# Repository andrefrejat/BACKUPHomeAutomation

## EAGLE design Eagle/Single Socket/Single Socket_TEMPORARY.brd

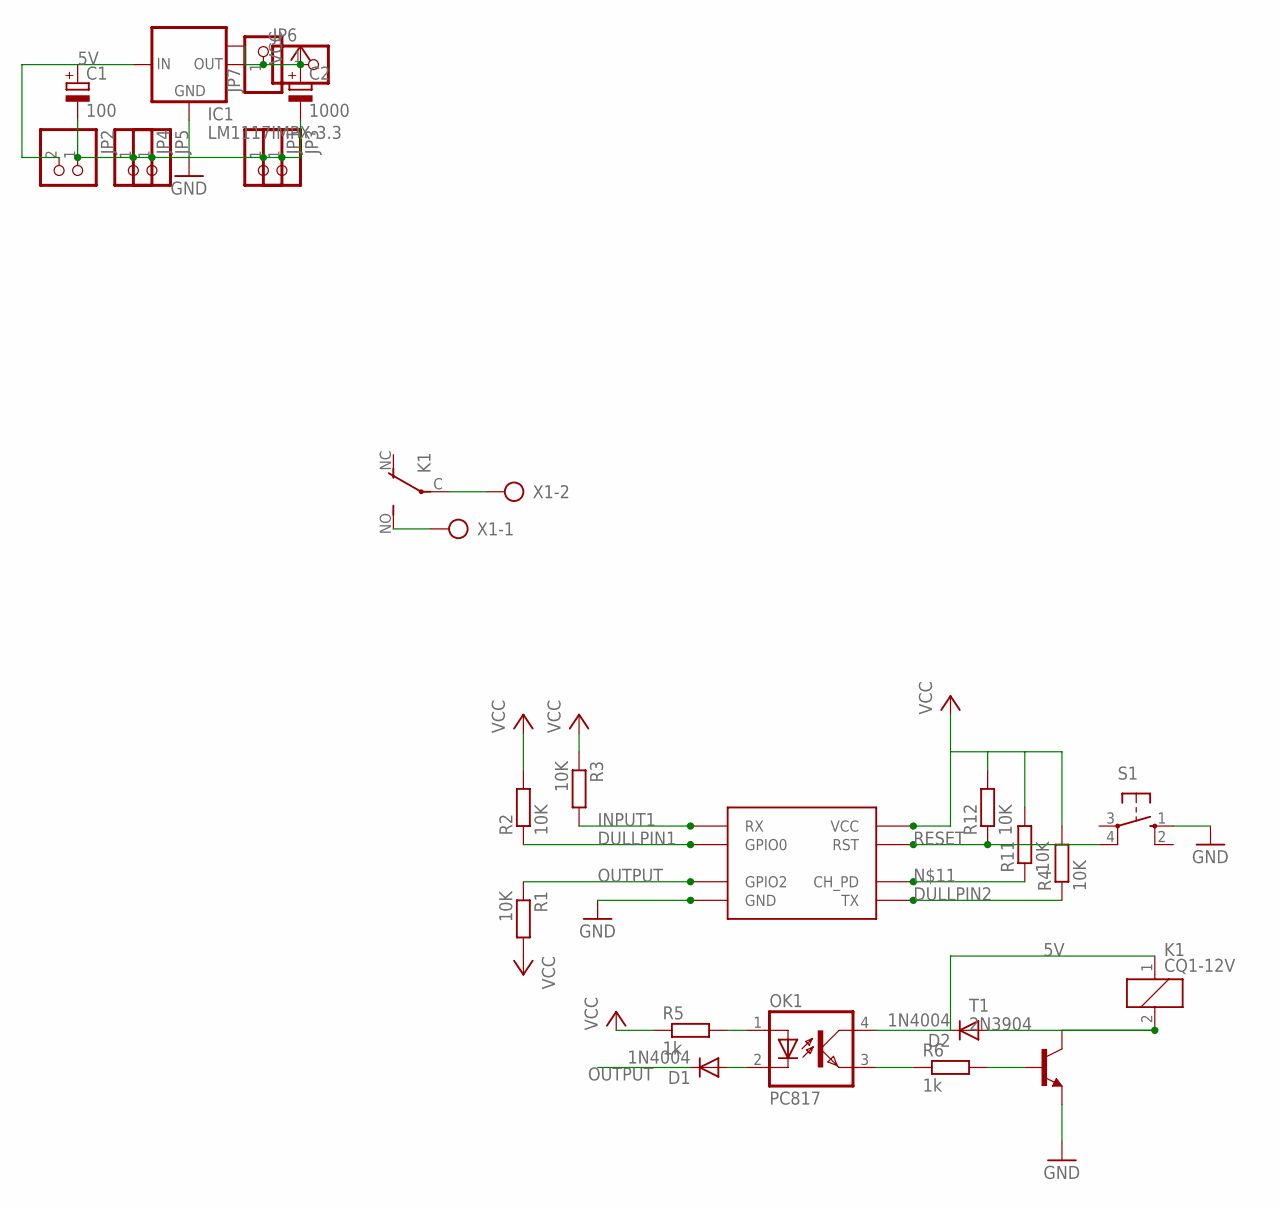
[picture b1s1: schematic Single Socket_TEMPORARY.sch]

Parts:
C1: 100; E5-10,5
C2: 1000; E5-10,5
D1, D2: 1N4004; DO41-10
IC1: LM1117IMPX-3.3; SOT223
JP1, JP3, JP4, JP5, JP6, JP7: PINHD-1X1; 1X01
JP2: PINHD-1X2; 1X02
K1: CQ1-12V; CQ1
OK1: PC817; DIL04
R1, R2, R3, R4, R11, R12: 10K; 0207/10
R5, R6: 1k; 0207/10
S1: 10-XX; B3F-10XX; MPN B3F-1000
T1: 2N3904; TO92
U$2: ESP8266
X1: AK500/2-H

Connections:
5V: C1.+, D2.C, IC1.3 (IN), JP2.2, K1.1, OK1.4 (COL)
DULLPIN1: R2.1, U$2.GPIO0
DULLPIN2: R4.1, U$2.TX
GND: C1.-, C2.-, IC1.1 (GND), JP1.1, JP2.1, JP3.1, JP4.1, JP5.1, S1.1 (S), T1.3 (E), U$2.GND
INPUT1: R3.2, U$2.RX
unnamed: K1.C, X1.2
unnamed: K1.NO (S), X1.1
unnamed: OK1.1 (A), R5.2
unnamed: OK1.3 (EMIT), R6.1
unnamed: D1.A, OK1.2 (C)
unnamed: R6.2, T1.2 (B)
unnamed: D2.A, K1.2, T1.1 (C)
unnamed: R11.1, U$2.CH_PD
OUTPUT: D1.C, R1.1, U$2.GPIO2
RESET: R12.1, S1.4 (P1), U$2.RST
VCC: C2.+, IC1.2 (OUT), IC1.TAB (OUT1), JP6.1, JP7.1, R1.2, R2.2, R3.1, R4.2, R5.1, R11.2, R12.2, U$2.VCC

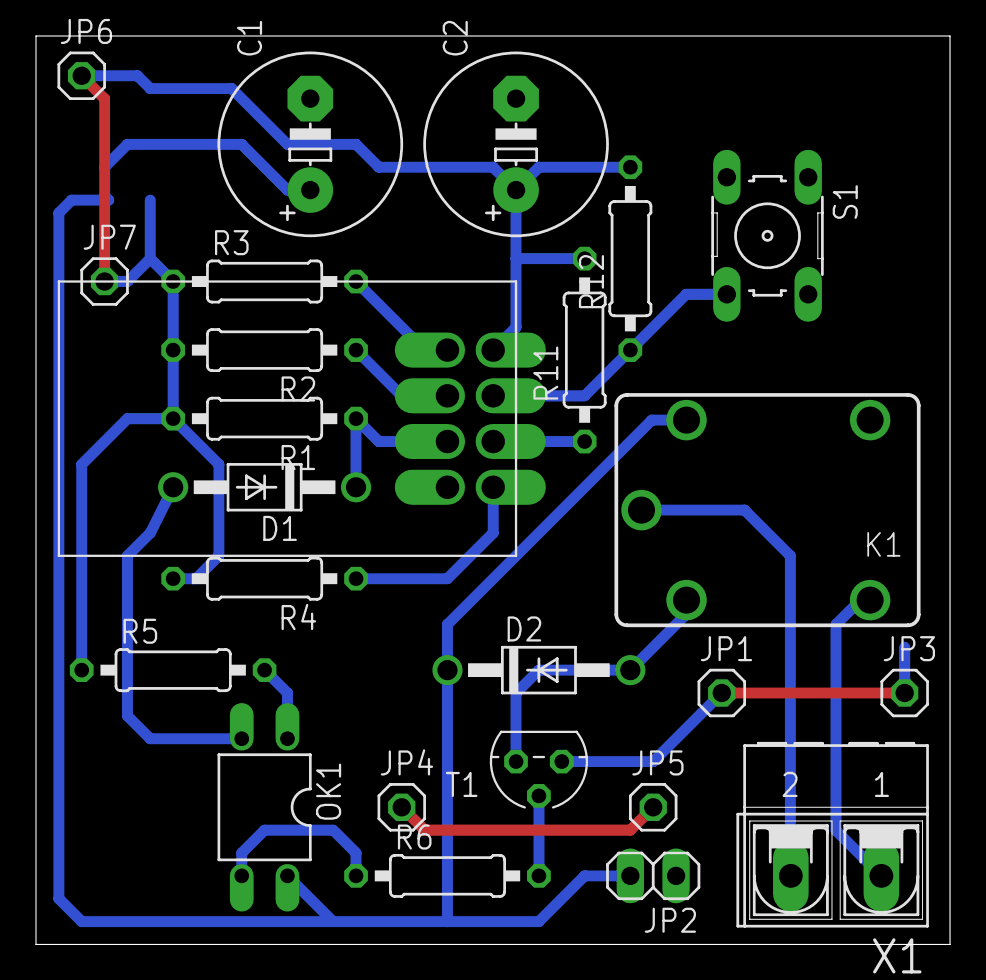
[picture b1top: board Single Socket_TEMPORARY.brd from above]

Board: 2 copper layers, 50.8 x 50.5 mm, 26 parts (1 on the bottom side), 16 nets.

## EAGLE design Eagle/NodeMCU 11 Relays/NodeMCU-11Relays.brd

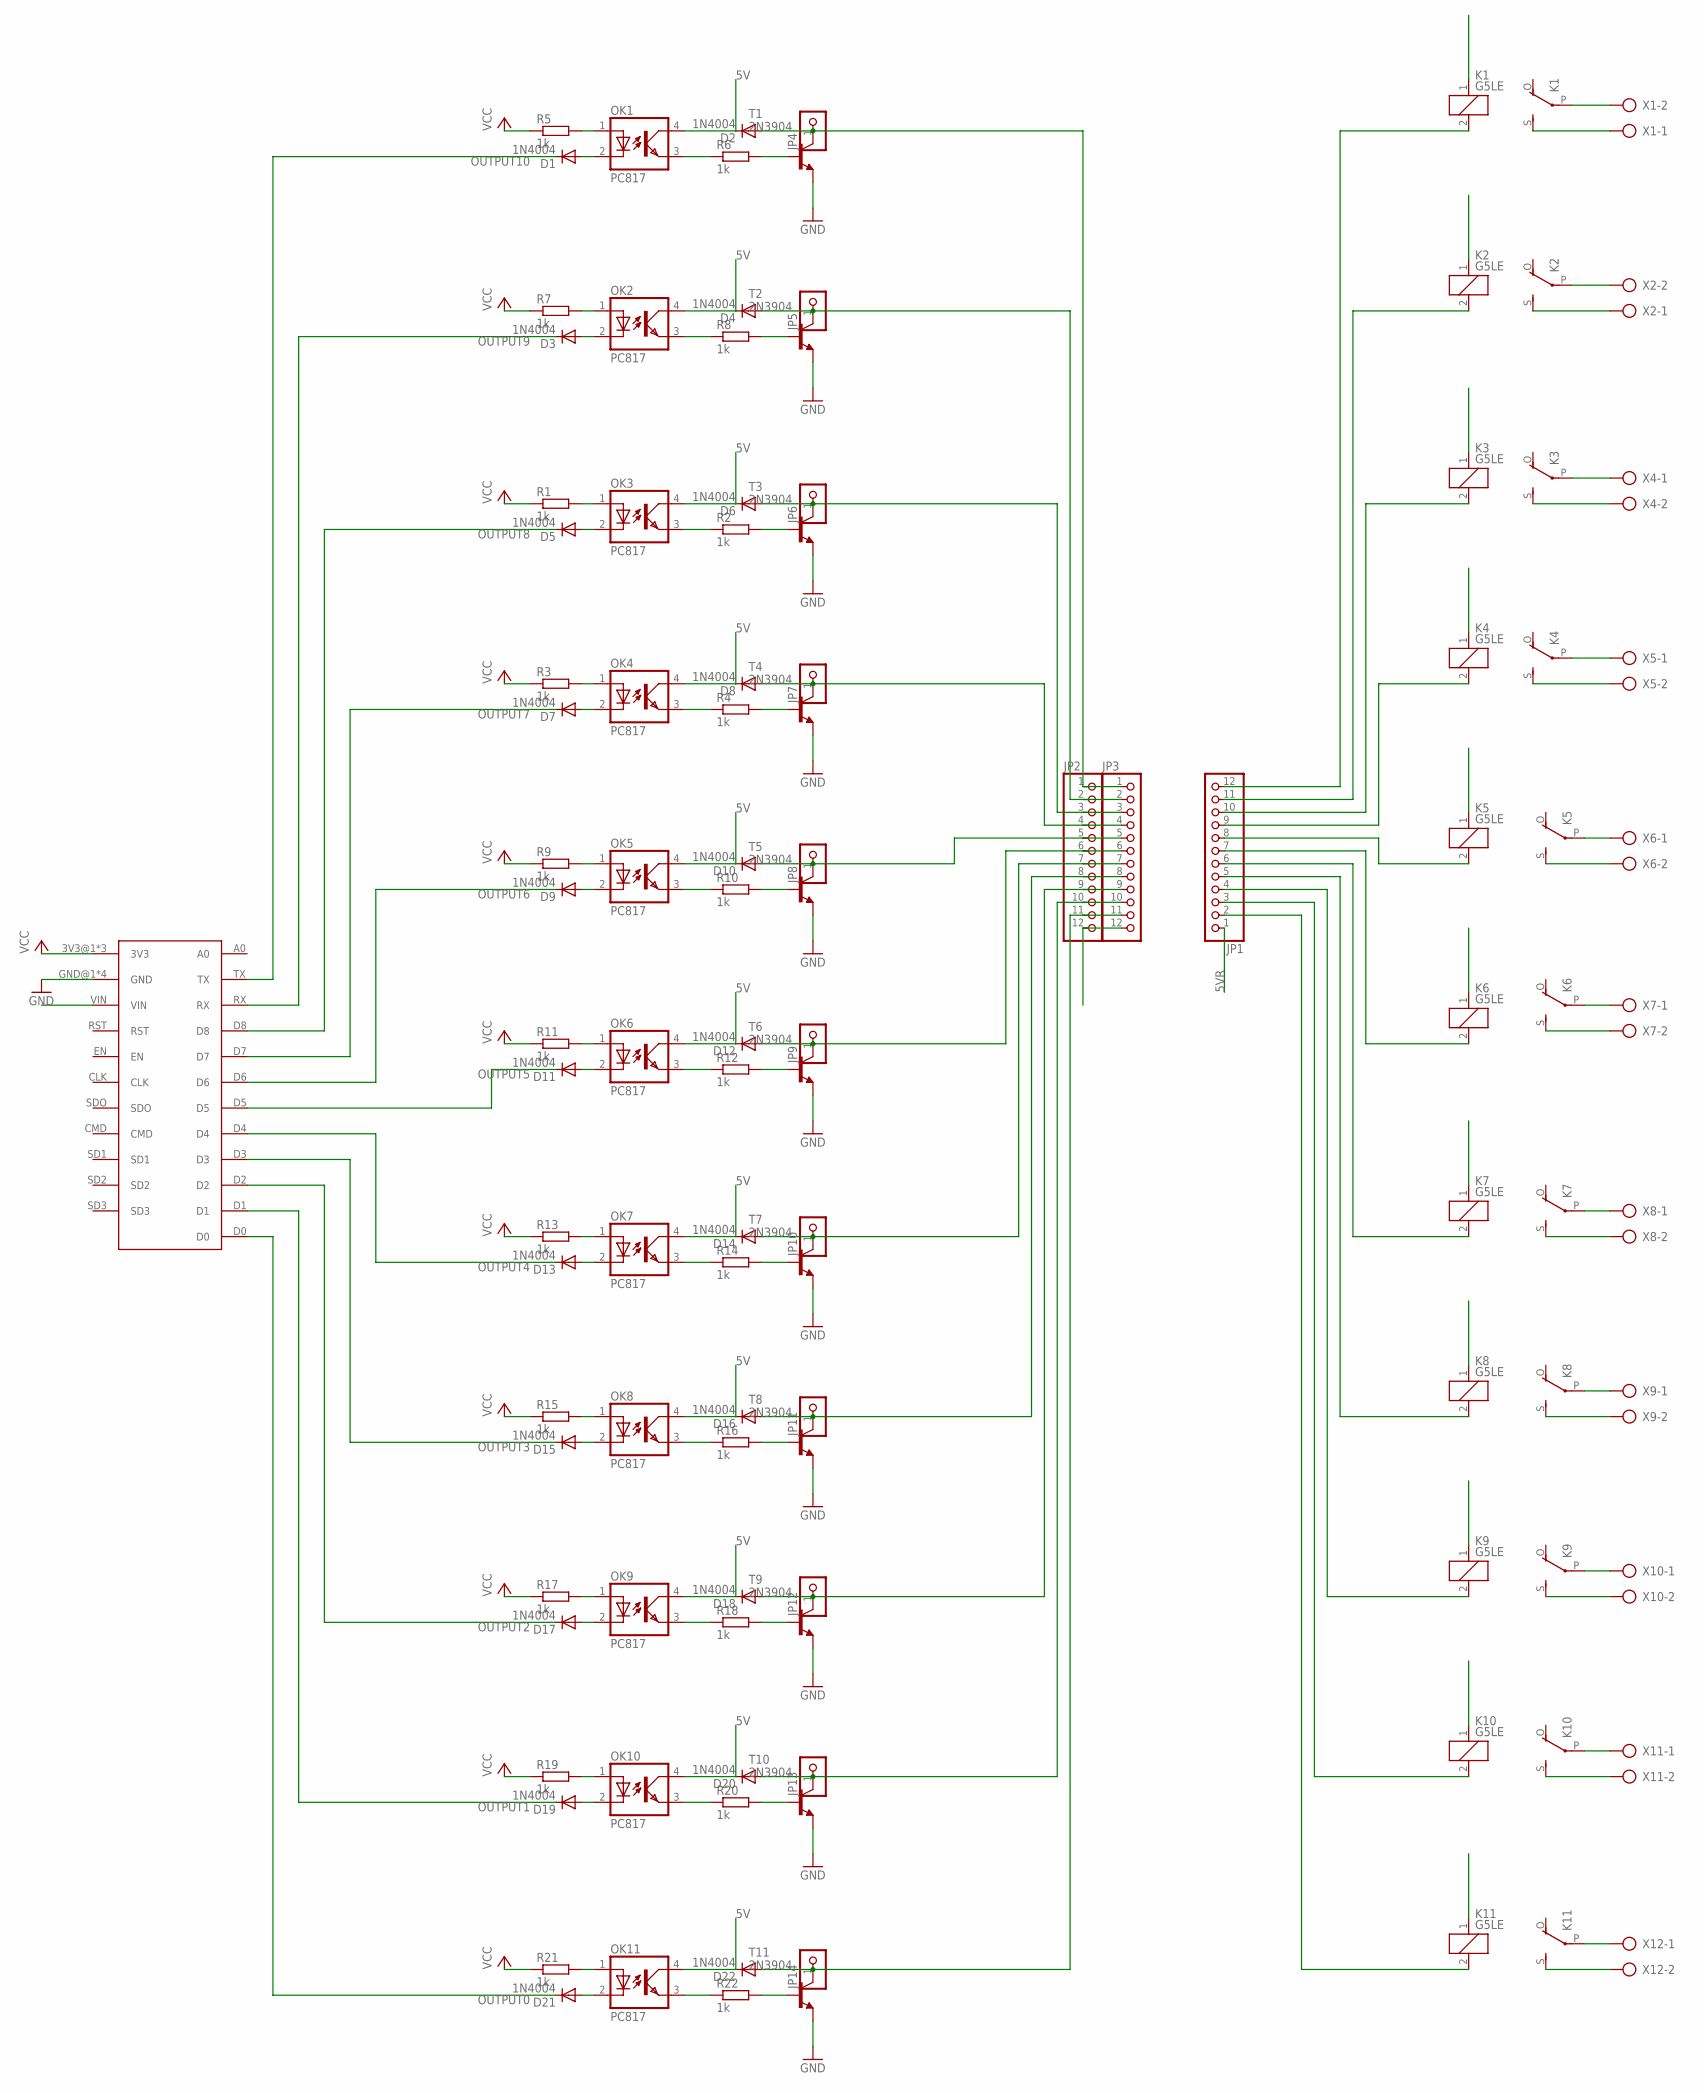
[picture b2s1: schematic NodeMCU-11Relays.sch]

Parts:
D1, D2, D3, D4, D5, D6, D7, D8, D9, D10, D11, D12, D13, D14, D15, D16, D17, D18, D19, D20, D21, D22: 1N4004; DO41-10
JP1, JP2, JP3: PINHD-1X12; 1X12
JP4, JP5, JP6, JP7, JP8, JP9, JP10, JP11, JP12, JP13, JP14: PINHD-1X1; 1X01
K1, K2, K3, K4, K5, K6, K7, K8, K9, K10, K11: G5LE
OK1, OK2, OK3, OK4, OK5, OK6, OK7, OK8, OK9, OK10, OK11: PC817; DIL04
R1, R2, R3, R4, R5, R6, R7, R8, R9, R10, R11, R12, R13, R14, R15, R16, R17, R18, R19, R20, R21, R22: 1k; 0207/10
T1, T2, T3, T4, T5, T6, T7, T8, T9, T10, T11: 2N3904; TO92
U$1: NODEMCU-1.0
X1, X2, X4, X5, X6, X7, X8, X9, X10, X11, X12: AK500/2-H

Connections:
5V: D2.C, D4.C, D6.C, D8.C, D10.C, D12.C, D14.C, D16.C, D18.C, D20.C, D22.C, JP2.12, JP3.12, OK1.4 (COL), OK2.4 (COL), OK3.4 (COL), OK4.4 (COL), OK5.4 (COL), OK6.4 (COL), OK7.4 (COL), OK8.4 (COL), OK9.4 (COL), OK10.4 (COL), OK11.4 (COL), U$1.VIN
5VR: JP1.1, K1.1, K2.1, K3.1, K4.1, K5.1, K6.1, K7.1, K8.1, K9.1, K11.1
GND: T1.3 (E), T2.3 (E), T3.3 (E), T4.3 (E), T5.3 (E), T6.3 (E), T7.3 (E), T8.3 (E), T9.3 (E), T10.3 (E), T11.3 (E), U$1.GND@1 (GND), U$1.GND@2 (GND), U$1.GND@3 (GND), U$1.GND@4 (GND)
unnamed: K1.P, X1.2
unnamed: K1.S, X1.1
unnamed: OK1.1 (A), R5.2
unnamed: OK1.3 (EMIT), R6.1
unnamed: D1.A, OK1.2 (C)
unnamed: OK2.1 (A), R7.2
unnamed: R6.2, T1.2 (B)
unnamed: D2.A, JP2.1, JP3.1, JP4.1, T1.1 (C)
unnamed: OK2.3 (EMIT), R8.1
unnamed: D3.A, OK2.2 (C)
unnamed: OK3.1 (A), R1.2
unnamed: R8.2, T2.2 (B)
unnamed: D4.A, JP2.2, JP3.2, JP5.1, T2.1 (C)
unnamed: K2.S, X2.1
unnamed: K2.P, X2.2
unnamed: OK3.3 (EMIT), R2.1
unnamed: D5.A, OK3.2 (C)
unnamed: R2.2, T3.2 (B)
unnamed: D6.A, JP2.3, JP3.3, JP6.1, T3.1 (C)
unnamed: OK4.1 (A), R3.2
unnamed: OK4.3 (EMIT), R4.1
unnamed: D7.A, OK4.2 (C)
unnamed: R4.2, T4.2 (B)
unnamed: D8.A, JP2.4, JP3.4, JP7.1, T4.1 (C)
unnamed: OK5.1 (A), R9.2
unnamed: OK5.3 (EMIT), R10.1
unnamed: D9.A, OK5.2 (C)
unnamed: R10.2, T5.2 (B)
unnamed: D10.A, JP2.5, JP3.5, JP8.1, T5.1 (C)
unnamed: OK6.1 (A), R11.2
unnamed: OK6.3 (EMIT), R12.1
unnamed: D11.A, OK6.2 (C)
unnamed: R12.2, T6.2 (B)
unnamed: D12.A, JP2.6, JP3.6, JP9.1, T6.1 (C)
unnamed: OK7.1 (A), R13.2
unnamed: OK7.3 (EMIT), R14.1
unnamed: D13.A, OK7.2 (C)
unnamed: R14.2, T7.2 (B)
unnamed: D14.A, JP2.7, JP3.7, JP10.1, T7.1 (C)
unnamed: OK8.1 (A), R15.2
unnamed: OK8.3 (EMIT), R16.1
unnamed: D15.A, OK8.2 (C)
unnamed: R16.2, T8.2 (B)
unnamed: D16.A, JP2.8, JP3.8, JP11.1, T8.1 (C)
unnamed: OK9.1 (A), R17.2
unnamed: OK9.3 (EMIT), R18.1
unnamed: D17.A, OK9.2 (C)
unnamed: R18.2, T9.2 (B)
unnamed: D18.A, JP2.9, JP3.9, JP12.1, T9.1 (C)
unnamed: OK10.1 (A), R19.2
unnamed: OK10.3 (EMIT), R20.1
unnamed: D19.A, OK10.2 (C)
unnamed: R20.2, T10.2 (B)
unnamed: D20.A, JP2.10, JP3.10, JP13.1, T10.1 (C)
unnamed: OK11.1 (A), R21.2
unnamed: OK11.3 (EMIT), R22.1
unnamed: D21.A, OK11.2 (C)
unnamed: R22.2, T11.2 (B)
unnamed: D22.A, JP2.11, JP3.11, JP14.1, T11.1 (C)
unnamed: K3.P, X4.1
unnamed: K4.P, X5.1
unnamed: K5.P, X6.1
unnamed: K6.P, X7.1
unnamed: K7.P, X8.1
unnamed: K8.P, X9.1
unnamed: K9.P, X10.1
unnamed: K10.P, X11.1
unnamed: K11.P, X12.1
unnamed: K3.S, X4.2
unnamed: K4.S, X5.2
unnamed: K5.S, X6.2
unnamed: K6.S, X7.2
unnamed: K7.S, X8.2
unnamed: K8.S, X9.2
unnamed: K9.S, X10.2
unnamed: K10.S, X11.2
unnamed: K11.S, X12.2
unnamed: JP1.2, K11.2
unnamed: JP1.3, K10.2
unnamed: JP1.4, K9.2
unnamed: JP1.5, K8.2
unnamed: JP1.6, K7.2
unnamed: JP1.7, K6.2
unnamed: JP1.8, K5.2
unnamed: JP1.9, K4.2
unnamed: JP1.10, K3.2
unnamed: JP1.11, K2.2
unnamed: JP1.12, K1.2
OUTPUT0: D21.C, U$1.D0
OUTPUT1: D19.C, U$1.D1
OUTPUT2: D17.C, U$1.D2
OUTPUT3: D15.C, U$1.D3
OUTPUT4: D13.C, U$1.D4
OUTPUT5: D11.C, U$1.D5
OUTPUT6: D9.C, U$1.D6
OUTPUT7: D7.C, U$1.D7
OUTPUT8: D5.C, U$1.D8
OUTPUT9: D3.C, U$1.RX
OUTPUT10: D1.C, U$1.TX
VCC: R1.1, R3.1, R5.1, R7.1, R9.1, R11.1, R13.1, R15.1, R17.1, R19.1, R21.1, U$1.3V3@1 (3V3), U$1.3V3@2 (3V3), U$1.3V3@3 (3V3)

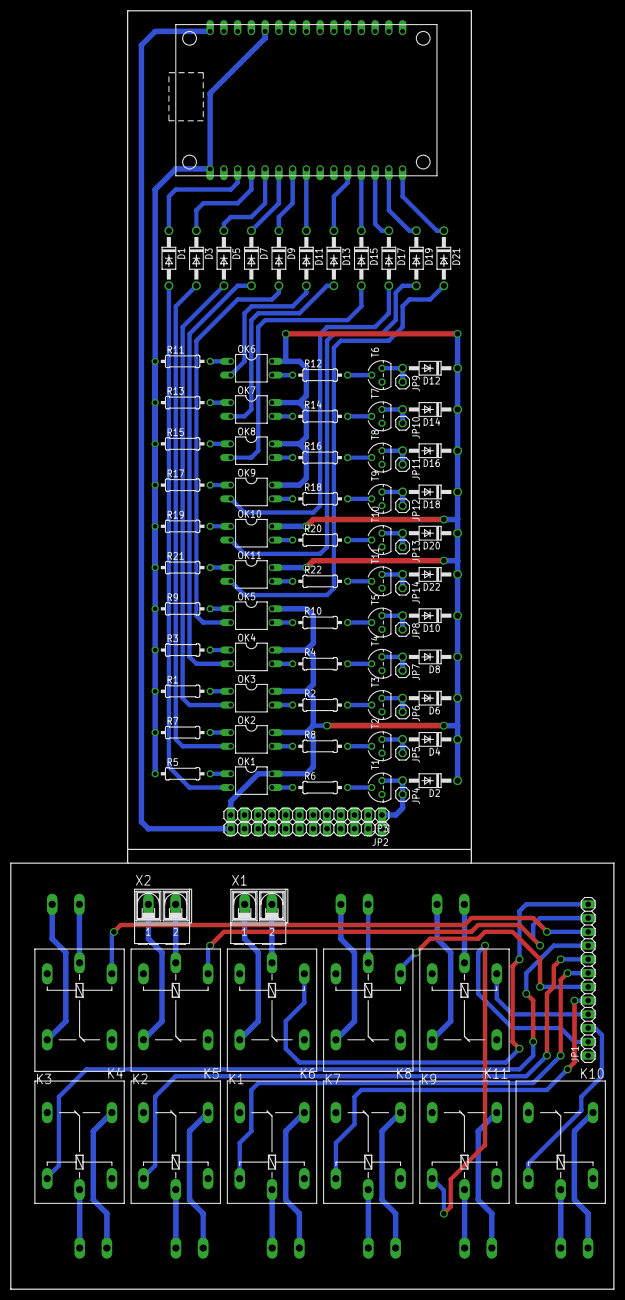
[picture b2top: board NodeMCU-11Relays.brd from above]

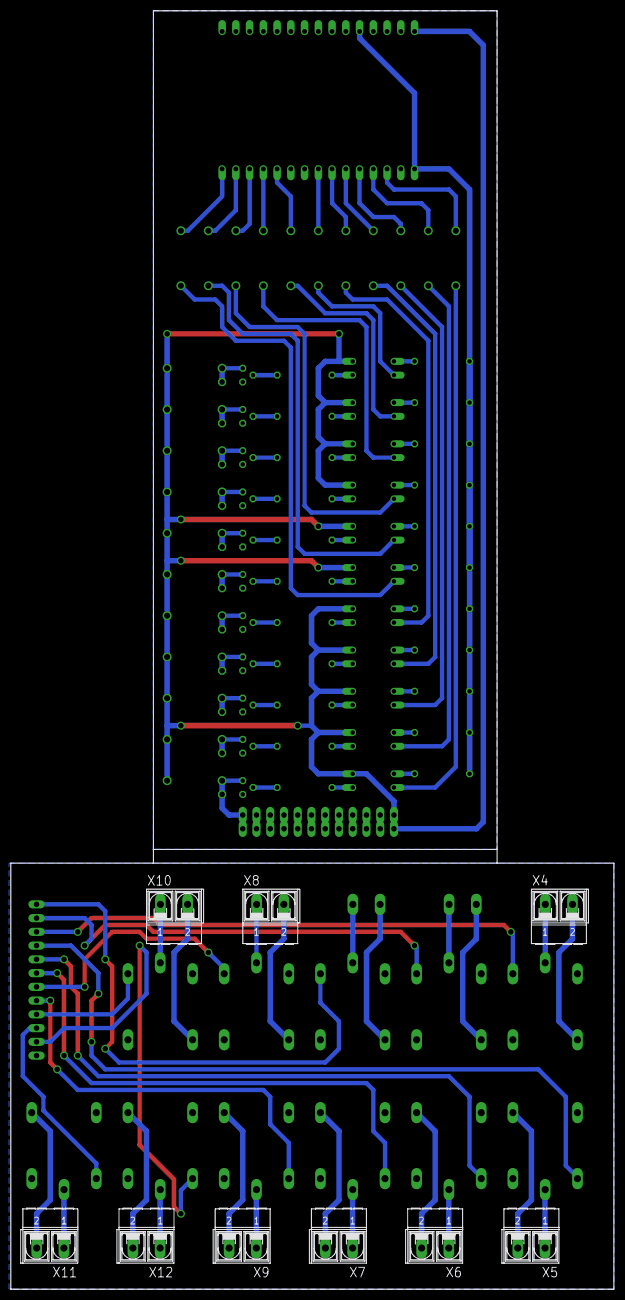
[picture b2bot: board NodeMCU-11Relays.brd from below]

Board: 2 copper layers, 111.4 x 236.2 mm, 103 parts (9 on the bottom side), 103 nets.

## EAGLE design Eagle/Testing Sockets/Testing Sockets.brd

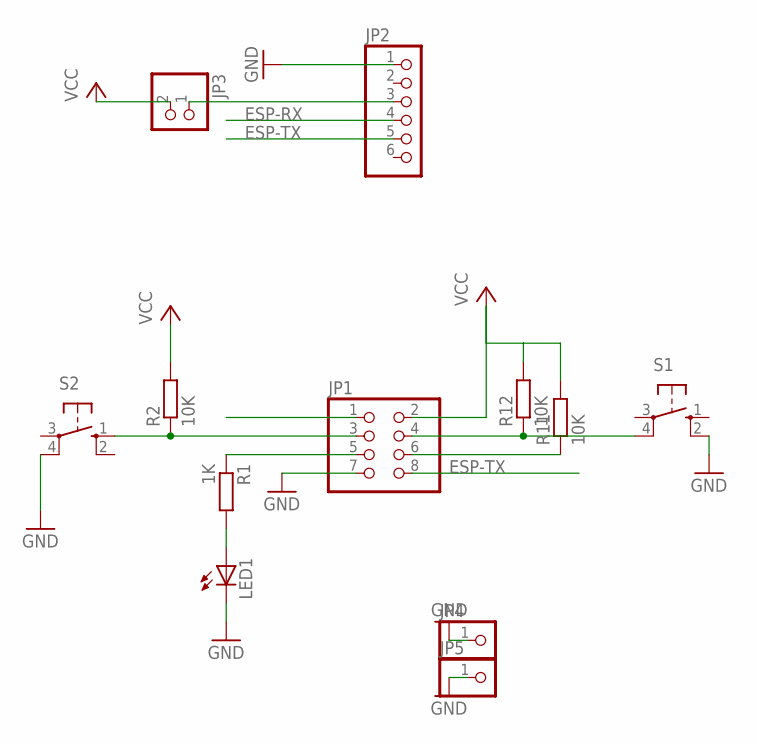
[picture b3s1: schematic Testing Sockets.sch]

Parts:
JP1: PINHD-2X4; 2X04
JP2: PINHD-1X6; 1X06
JP3: PINHD-1X2; 1X02
JP4, JP5: PINHD-1X1; 1X01
LED1: LED5MM
R1: 1K; 0207/10
R2, R11, R12: 10K; 0207/10
S1: 10-XX; B3F-10XX
S2: 10-XX; B3F-10XX; MPN B3F-1000

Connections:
ESP-RX: JP1.1, JP2.4
ESP-TX: JP1.8, JP2.5
GND: JP1.7, JP2.1, JP4.1, JP5.1, LED1.K (C), S1.2 (S1), S2.4 (P1)
unnamed: JP1.5, R1.1
unnamed: LED1.A, R1.2
unnamed: JP2.3, JP3.1
unnamed: JP1.6, R11.1
unnamed: JP1.4, R12.1, S1.4 (P1)
SOCKET1: JP1.3, R2.1, S2.1 (S)
VCC: JP1.2, JP3.2, R2.2, R11.2, R12.2

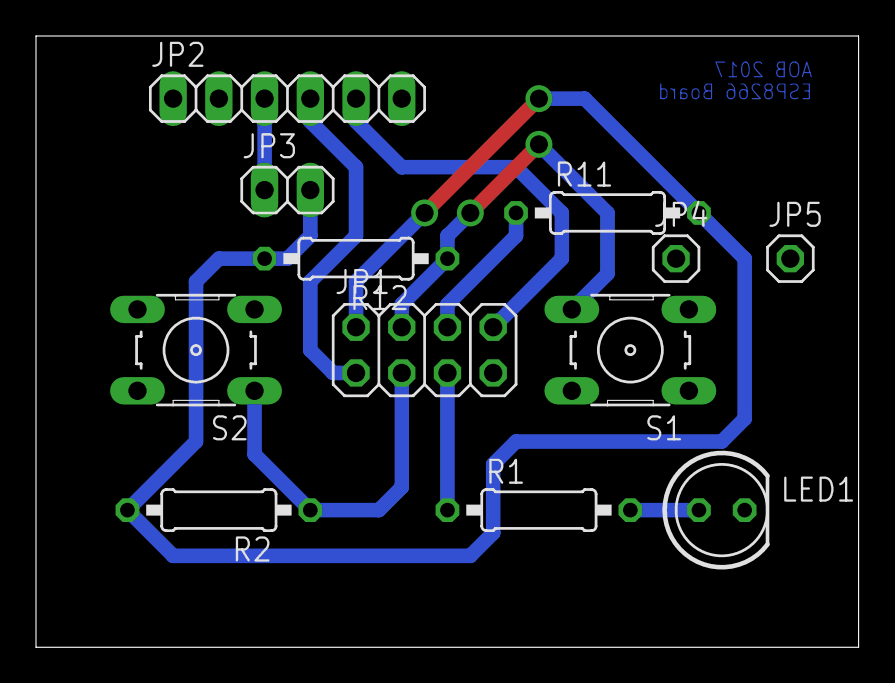
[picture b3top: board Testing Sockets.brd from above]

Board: 2 copper layers, 45.7 x 34.0 mm, 12 parts (0 on the bottom side), 10 nets.

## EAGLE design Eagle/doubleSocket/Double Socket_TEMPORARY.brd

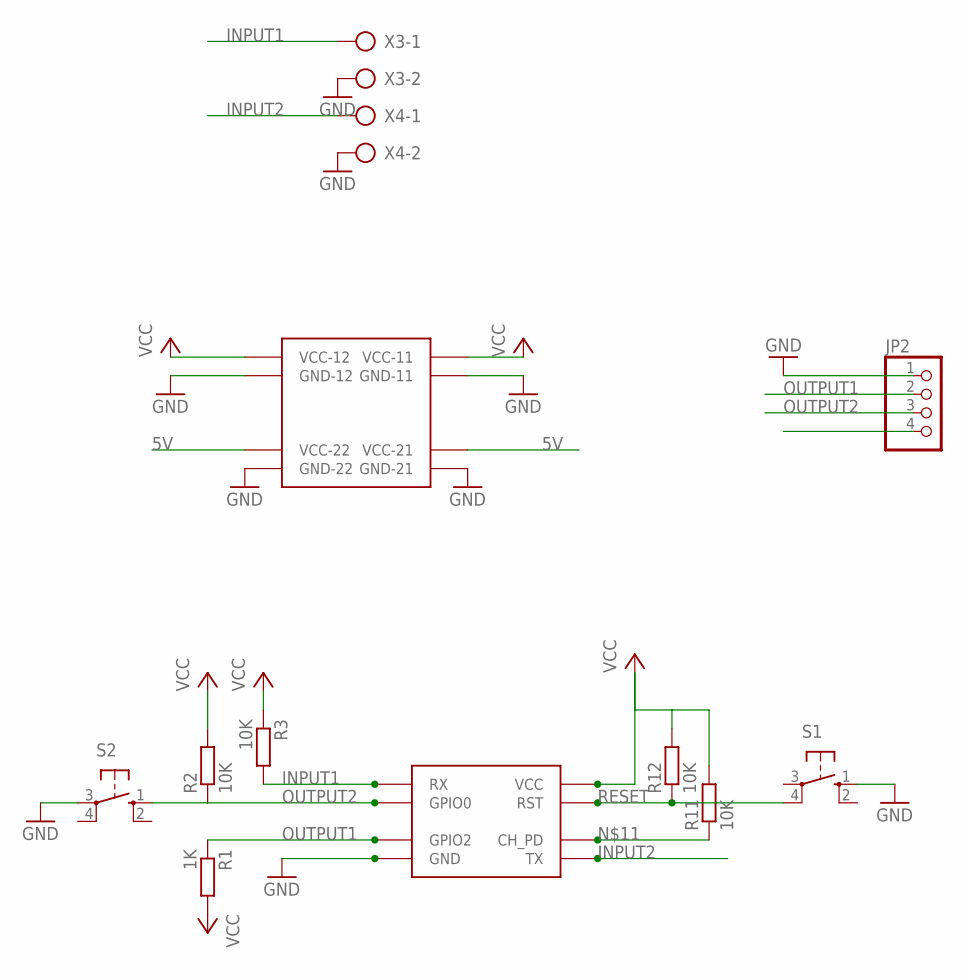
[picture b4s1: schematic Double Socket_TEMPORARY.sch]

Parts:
JP2: PINHD-1X4; 1X04
R1: 1K; 0207/10
R2, R3, R11, R12: 10K; 0207/10
S1, S2: 40-XX; B3F-40XX; MPN B3F-4000
U$1: YWROBOT
U$2: ESP8266
X3, X4: AK500/2-H

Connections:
5V: JP2.4, U$1.VCC-21, U$1.VCC-22
GND: JP2.1, S1.1 (S), S2.3, U$1.GND-11, U$1.GND-12, U$1.GND-21, U$1.GND-22, U$2.GND, X3.2, X4.2
INPUT1: R3.2, U$2.RX, X3.1
INPUT2: U$2.TX, X4.1
unnamed: R11.1, U$2.CH_PD
OUTPUT1: JP2.2, R1.1, U$2.GPIO2
OUTPUT2: JP2.3, R2.1, S2.1 (S), U$2.GPIO0
RESET: R12.1, S1.4 (P1), U$2.RST
VCC: R1.2, R2.2, R3.1, R11.2, R12.2, U$1.VCC-11, U$1.VCC-12, U$2.VCC

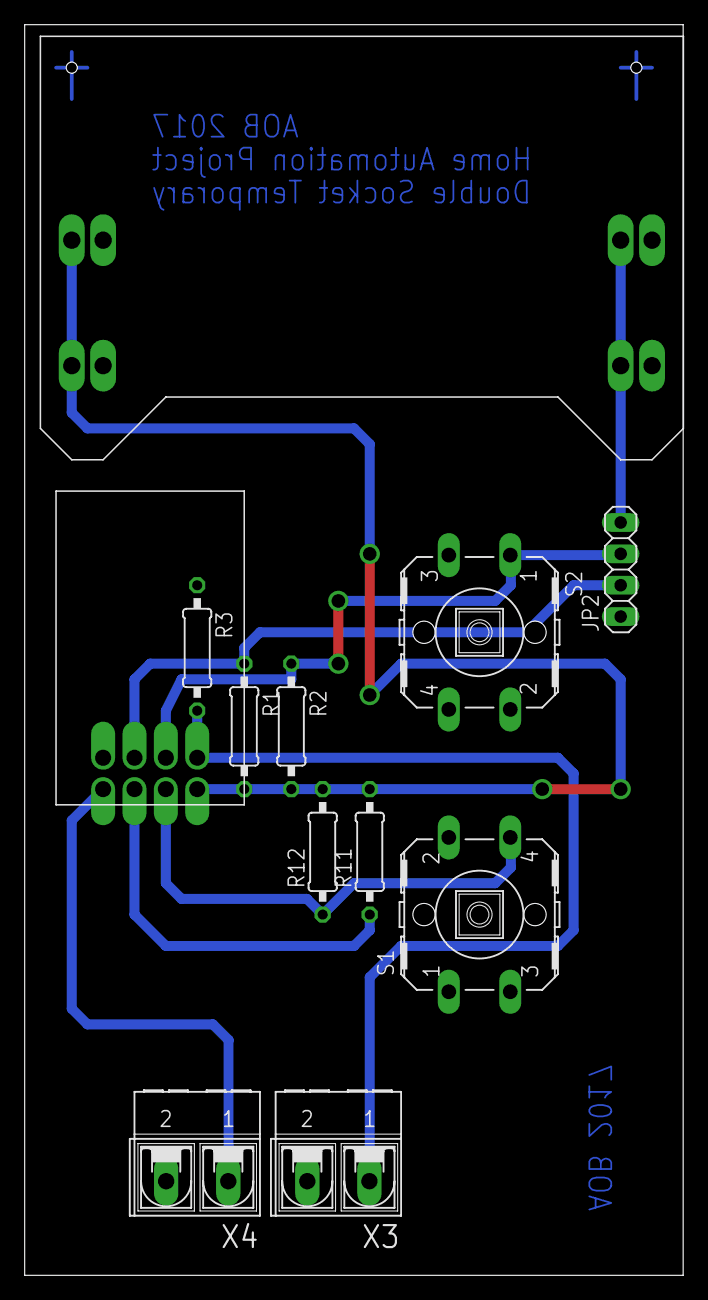
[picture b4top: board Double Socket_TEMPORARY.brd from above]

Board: 2 copper layers, 53.3 x 101.3 mm, 12 parts (0 on the bottom side), 9 nets.
